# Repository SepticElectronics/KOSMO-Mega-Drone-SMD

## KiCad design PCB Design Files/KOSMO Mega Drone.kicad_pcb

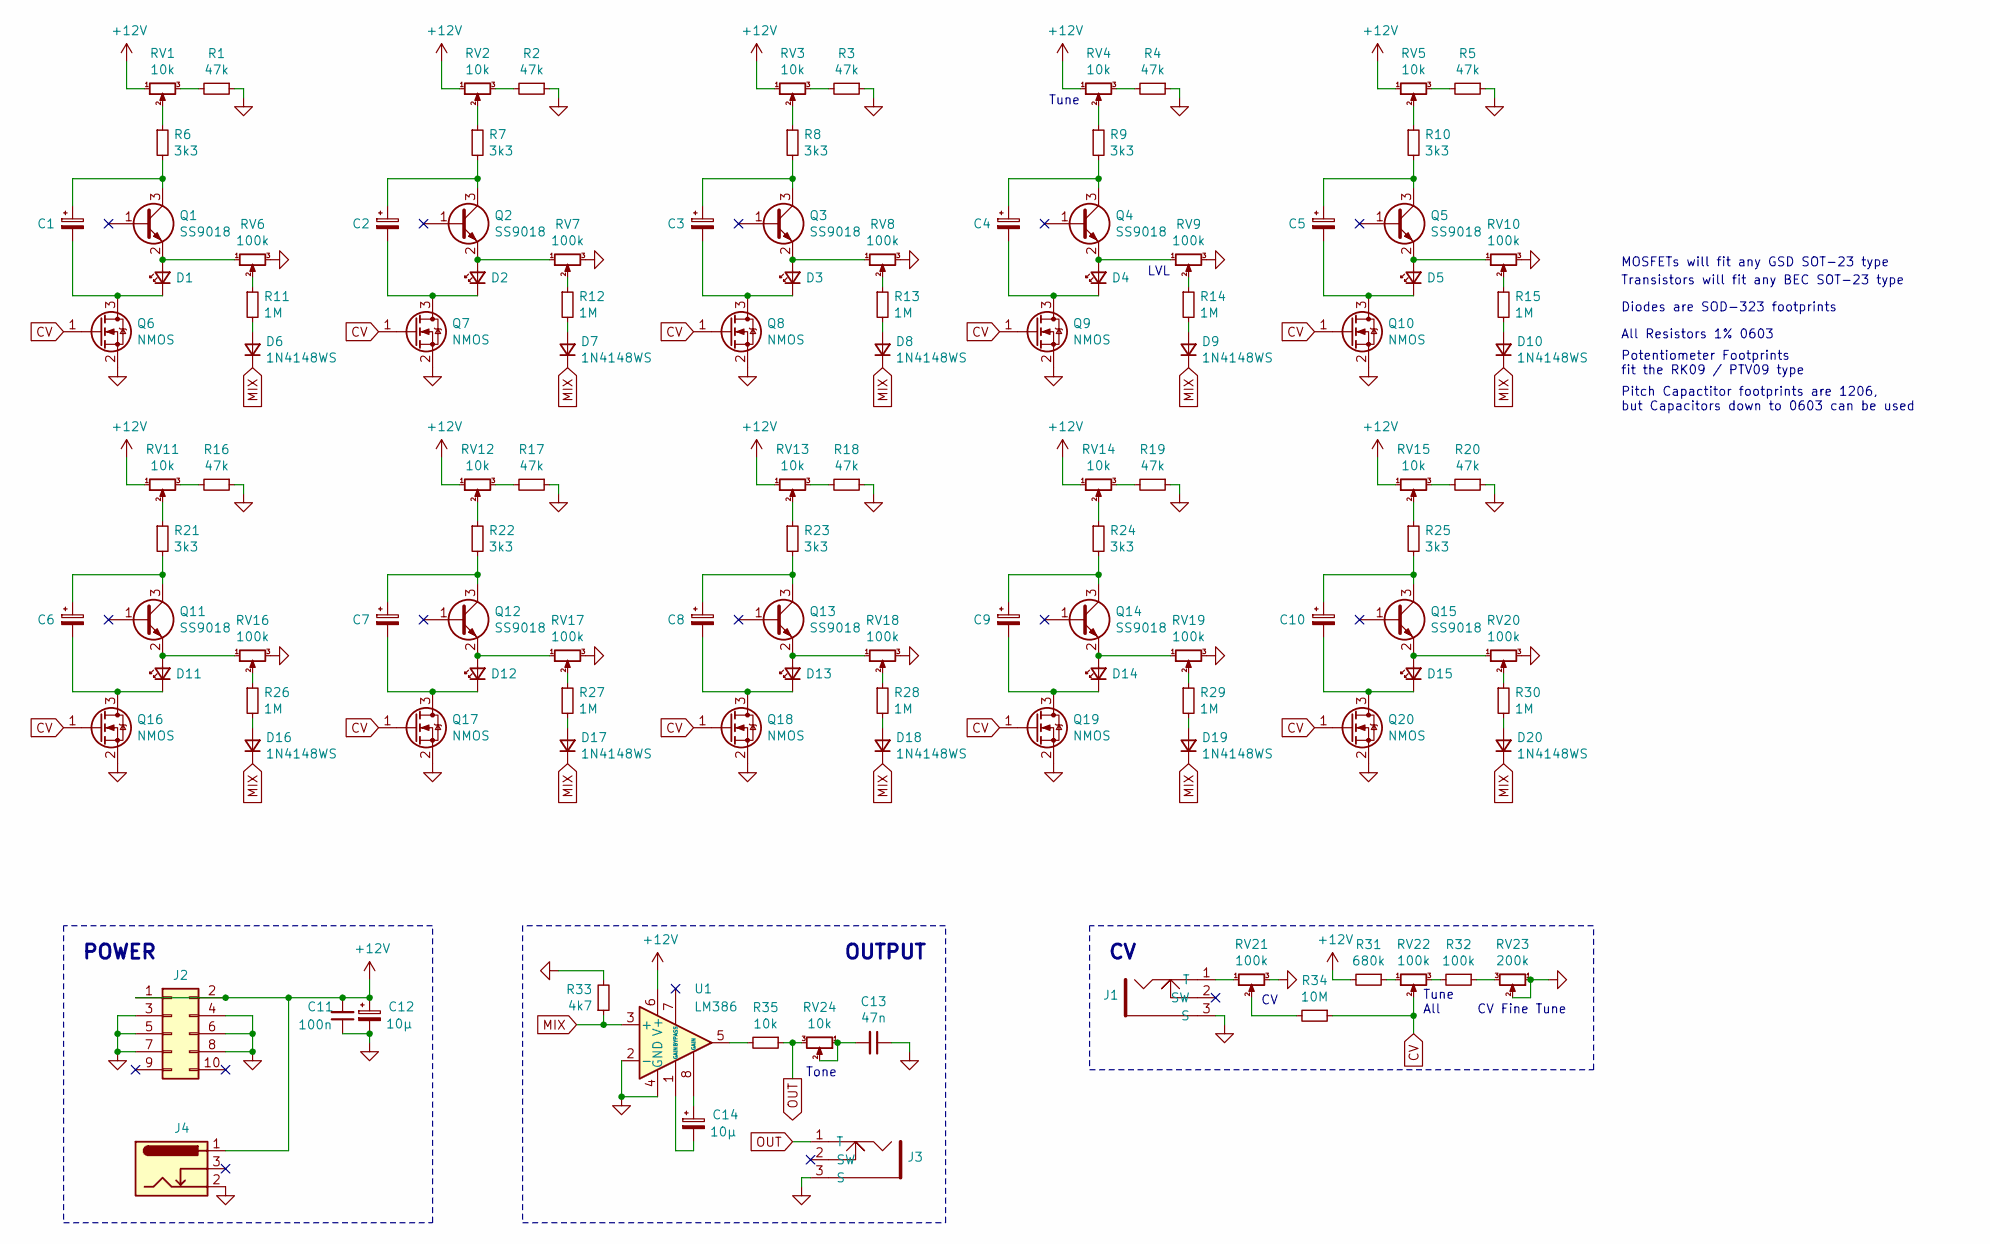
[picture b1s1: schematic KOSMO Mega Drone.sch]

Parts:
C1, C2, C3, C4, C5, C6, C7, C8, C9, C10: CP_Small; C_1206_3216Metric
C11: 100n; C_0603_1608Metric
C12, C14: 10µ; CP_Radial_D5.0mm_P2.50mm
C13: 47n; C_0603_1608Metric
D1, D2, D3, D4, D5, D11, D12, D13, D14, D15: LED_Small; LED_D3.0mm
D6, D7, D8, D9, D10, D16, D17, D18, D19, D20: 1N4148WS; D_SOD-323
J1, J3: 3.5mm_Jacksocket_Mono; 3.5mm_Mono_Jacksocket
J2: Conn_02x05_Odd_Even; PinHeader_2x05_P2.54mm_Vertical
J4: Barrel_Jack_Switch; BarrelJack_Wuerth_6941xx301002
Q1, Q2, Q3, Q4, Q5, Q11, Q12, Q13, Q14, Q15: SS9018; SOT-23
Q6, Q7, Q8, Q9, Q10, Q16, Q17, Q18, Q19, Q20: NMOS; SOT-23
R1, R2, R3, R4, R5, R16, R17, R18, R19, R20: 47k; R_0603_1608Metric
R6, R7, R8, R9, R10, R21, R22, R23, R24, R25: 3k3; R_0603_1608Metric
R11, R12, R13, R14, R15, R26, R27, R28, R29, R30: 1M; R_0603_1608Metric
R31: 680k; R_0603_1608Metric
R32: 100k; R_0603_1608Metric
R33: 4k7; R_0603_1608Metric
R34: 10M; R_0603_1608Metric
R35: 10k; R_0603_1608Metric
RV1, RV2, RV3, RV4, RV5, RV11, RV12, RV13, RV14, RV15, RV24: 10k; Potentiometer_Alps_RK09K_Single_Vertical
RV6, RV7, RV8, RV9, RV10, RV16, RV17, RV18, RV19, RV20, RV21, RV22: 100k; Potentiometer_Alps_RK09K_Single_Vertical
RV23: 200k; Potentiometer_Alps_RK09K_Single_Vertical
U1: LM386; SOIC-8_3.9x4.9mm_P1.27mm

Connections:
+12V: C11.2, C12.1, J2.1, J2.2, J4.1, R31.2, RV1.1, RV2.1, RV3.1, RV4.1, RV5.1, RV11.1, RV12.1, RV13.1, RV14.1, RV15.1, U1.6 (V+)
CV: Q6.1 (G), Q7.1 (G), Q8.1 (G), Q9.1 (G), Q10.1 (G), Q16.1 (G), Q17.1 (G), Q18.1 (G), Q19.1 (G), Q20.1 (G), R34.1, RV22.2
GND: C11.1, C12.2, C13.1, J1.3 (S), J2.3, J2.4, J2.5, J2.6, J2.7, J2.8, J3.3 (S), J4.2, Q6.2 (S), Q7.2 (S), Q8.2 (S), Q9.2 (S), Q10.2 (S), Q16.2 (S), Q17.2 (S), Q18.2 (S), Q19.2 (S), Q20.2 (S), R1.1, R2.1, R3.1, R4.1, R5.1, R16.1, R17.1, R18.1, R19.1, R20.1, R33.2, RV6.3, RV7.3, RV8.3, RV9.3, RV10.3, RV16.3, RV17.3, RV18.3, RV19.3, RV20.3, RV21.3, RV23.1, RV23.2, U1.2 (-), U1.4 (GND)
MIX: D6.1 (K), D7.1 (K), D8.1 (K), D9.1 (K), D10.1 (K), D16.1 (K), D17.1 (K), D18.1 (K), D19.1 (K), D20.1 (K), R33.1, U1.3 (+)
unnamed: C1.1, Q1.3 (C), R6.2
unnamed: C1.2, D1.1 (K), Q6.3 (D)
unnamed: C2.1, Q2.3 (C), R7.2
unnamed: C2.2, D2.1 (K), Q7.3 (D)
unnamed: C3.1, Q3.3 (C), R8.2
unnamed: C3.2, D3.1 (K), Q8.3 (D)
unnamed: C4.1, Q4.3 (C), R9.2
unnamed: C4.2, D4.1 (K), Q9.3 (D)
unnamed: C5.1, Q5.3 (C), R10.2
unnamed: C5.2, D5.1 (K), Q10.3 (D)
unnamed: C6.1, Q11.3 (C), R21.2
unnamed: C6.2, D11.1 (K), Q16.3 (D)
unnamed: C7.1, Q12.3 (C), R22.2
unnamed: C7.2, D12.1 (K), Q17.3 (D)
unnamed: C8.1, Q13.3 (C), R23.2
unnamed: C8.2, D13.1 (K), Q18.3 (D)
unnamed: C9.1, Q14.3 (C), R24.2
unnamed: C9.2, D14.1 (K), Q19.3 (D)
unnamed: C10.1, Q15.3 (C), R25.2
unnamed: C10.2, D15.1 (K), Q20.3 (D)
unnamed: C13.2, RV24.1, RV24.2
unnamed: C14.1, U1.8 (GAIN)
unnamed: C14.2, U1.1 (GAIN)
unnamed: D1.2 (A), Q1.2 (E), RV6.1
unnamed: D2.2 (A), Q2.2 (E), RV7.1
unnamed: D3.2 (A), Q3.2 (E), RV8.1
unnamed: D4.2 (A), Q4.2 (E), RV9.1
unnamed: D5.2 (A), Q5.2 (E), RV10.1
unnamed: D6.2 (A), R11.2
unnamed: D7.2 (A), R12.2
unnamed: D8.2 (A), R13.2
unnamed: D9.2 (A), R14.2
unnamed: D10.2 (A), R15.2
unnamed: D11.2 (A), Q11.2 (E), RV16.1
unnamed: D12.2 (A), Q12.2 (E), RV17.1
unnamed: D13.2 (A), Q13.2 (E), RV18.1
unnamed: D14.2 (A), Q14.2 (E), RV19.1
unnamed: D15.2 (A), Q15.2 (E), RV20.1
unnamed: D16.2 (A), R26.2
unnamed: D17.2 (A), R27.2
unnamed: D18.2 (A), R28.2
unnamed: D19.2 (A), R29.2
unnamed: D20.2 (A), R30.2
unnamed: J1.1 (T), RV21.1
unnamed: R1.2, RV1.3
unnamed: R2.2, RV2.3
unnamed: R3.2, RV3.3
unnamed: R4.2, RV4.3
unnamed: R5.2, RV5.3
unnamed: R6.1, RV1.2
unnamed: R7.1, RV2.2
unnamed: R8.1, RV3.2
unnamed: R9.1, RV4.2
unnamed: R10.1, RV5.2
unnamed: R11.1, RV6.2
unnamed: R12.1, RV7.2
unnamed: R13.1, RV8.2
unnamed: R14.1, RV9.2
unnamed: R15.1, RV10.2
unnamed: R16.2, RV11.3
unnamed: R17.2, RV12.3
unnamed: R18.2, RV13.3
unnamed: R19.2, RV14.3
unnamed: R20.2, RV15.3
unnamed: R21.1, RV11.2
unnamed: R22.1, RV12.2
unnamed: R23.1, RV13.2
unnamed: R24.1, RV14.2
unnamed: R25.1, RV15.2
unnamed: R26.1, RV16.2
unnamed: R27.1, RV17.2
unnamed: R28.1, RV18.2
unnamed: R29.1, RV19.2
unnamed: R30.1, RV20.2
unnamed: R31.1, RV22.1
unnamed: R32.1, RV23.3
unnamed: R32.2, RV22.3
unnamed: R34.2, RV21.2
unnamed: R35.2, U1.5
OUT: J3.1 (T), R35.1, RV24.3

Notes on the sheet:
Tune
LVL
Tone
CV Fine Tune
Tune All
All Resistors 1% 0603
Potentiometer Footprints fit the RK09 / PTV09 type
Transistors will fit any BEC SOT-23 type
Diodes are SOD-323 footprints
Pitch Capactitor footprints are 1206, but Capacitors down to 0603 can be used
OUTPUT
POWER
MOSFETs will fit any GSD SOT-23 type

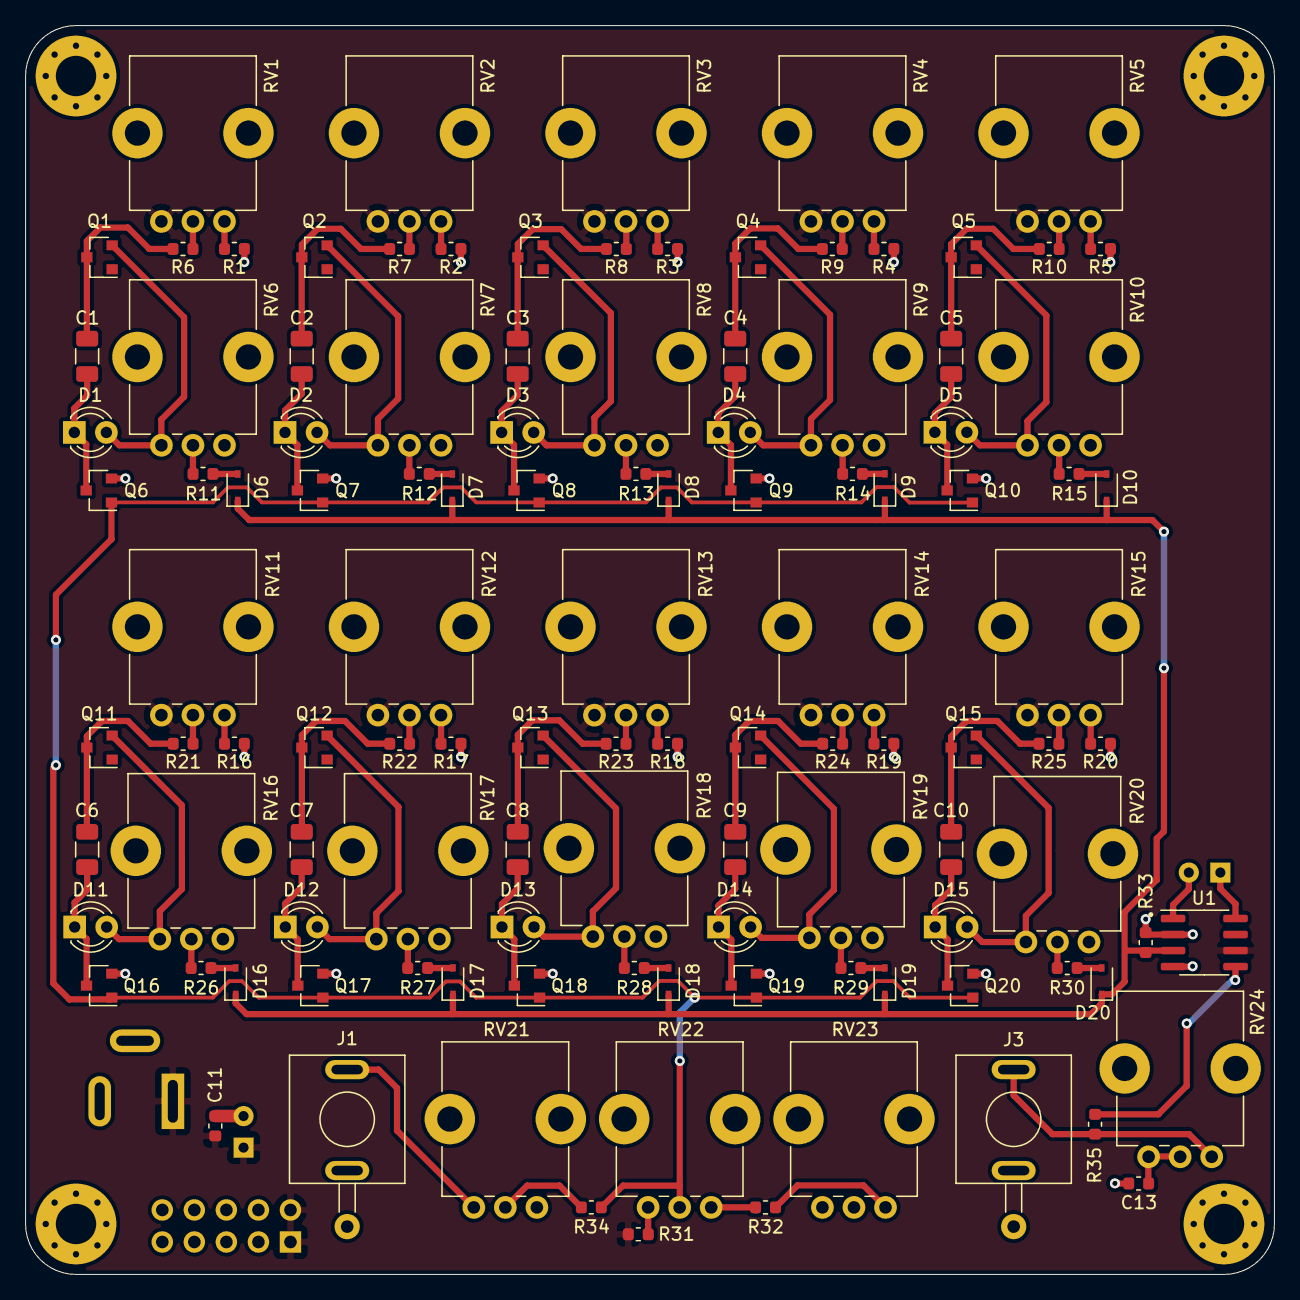
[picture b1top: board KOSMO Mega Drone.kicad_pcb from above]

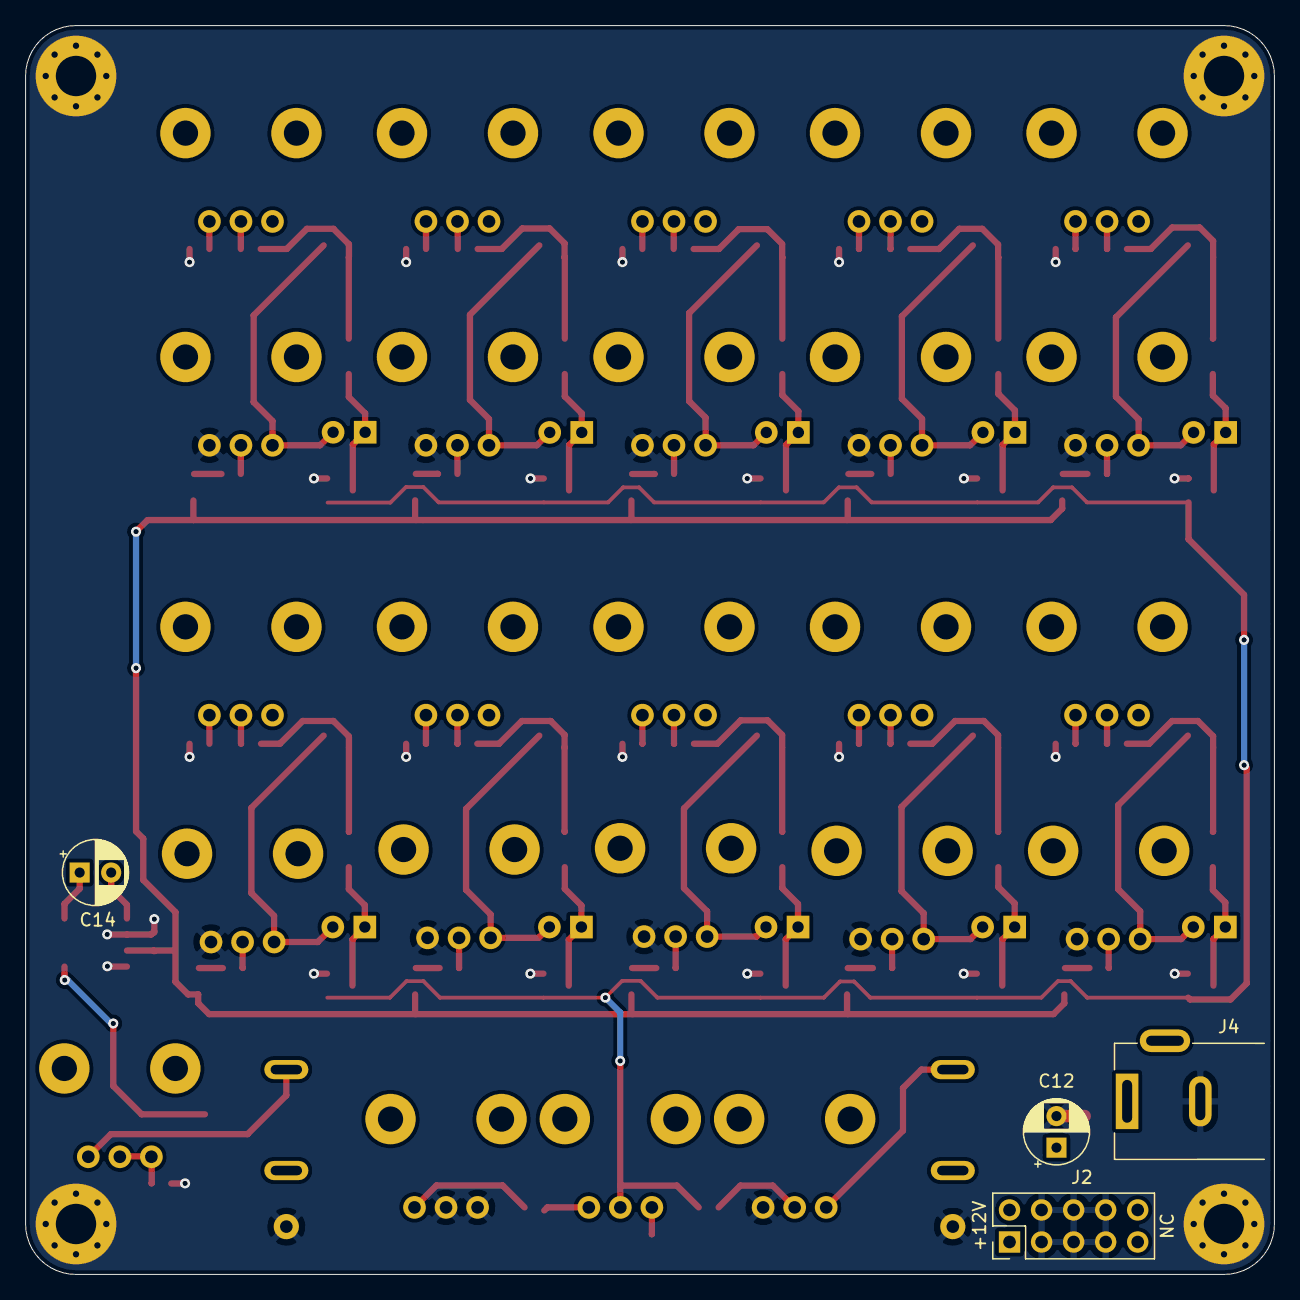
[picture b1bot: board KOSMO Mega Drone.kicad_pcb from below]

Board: 2 copper layers, 99.0 x 99.0 mm, 118 parts (4 on the bottom side), 84 nets.
